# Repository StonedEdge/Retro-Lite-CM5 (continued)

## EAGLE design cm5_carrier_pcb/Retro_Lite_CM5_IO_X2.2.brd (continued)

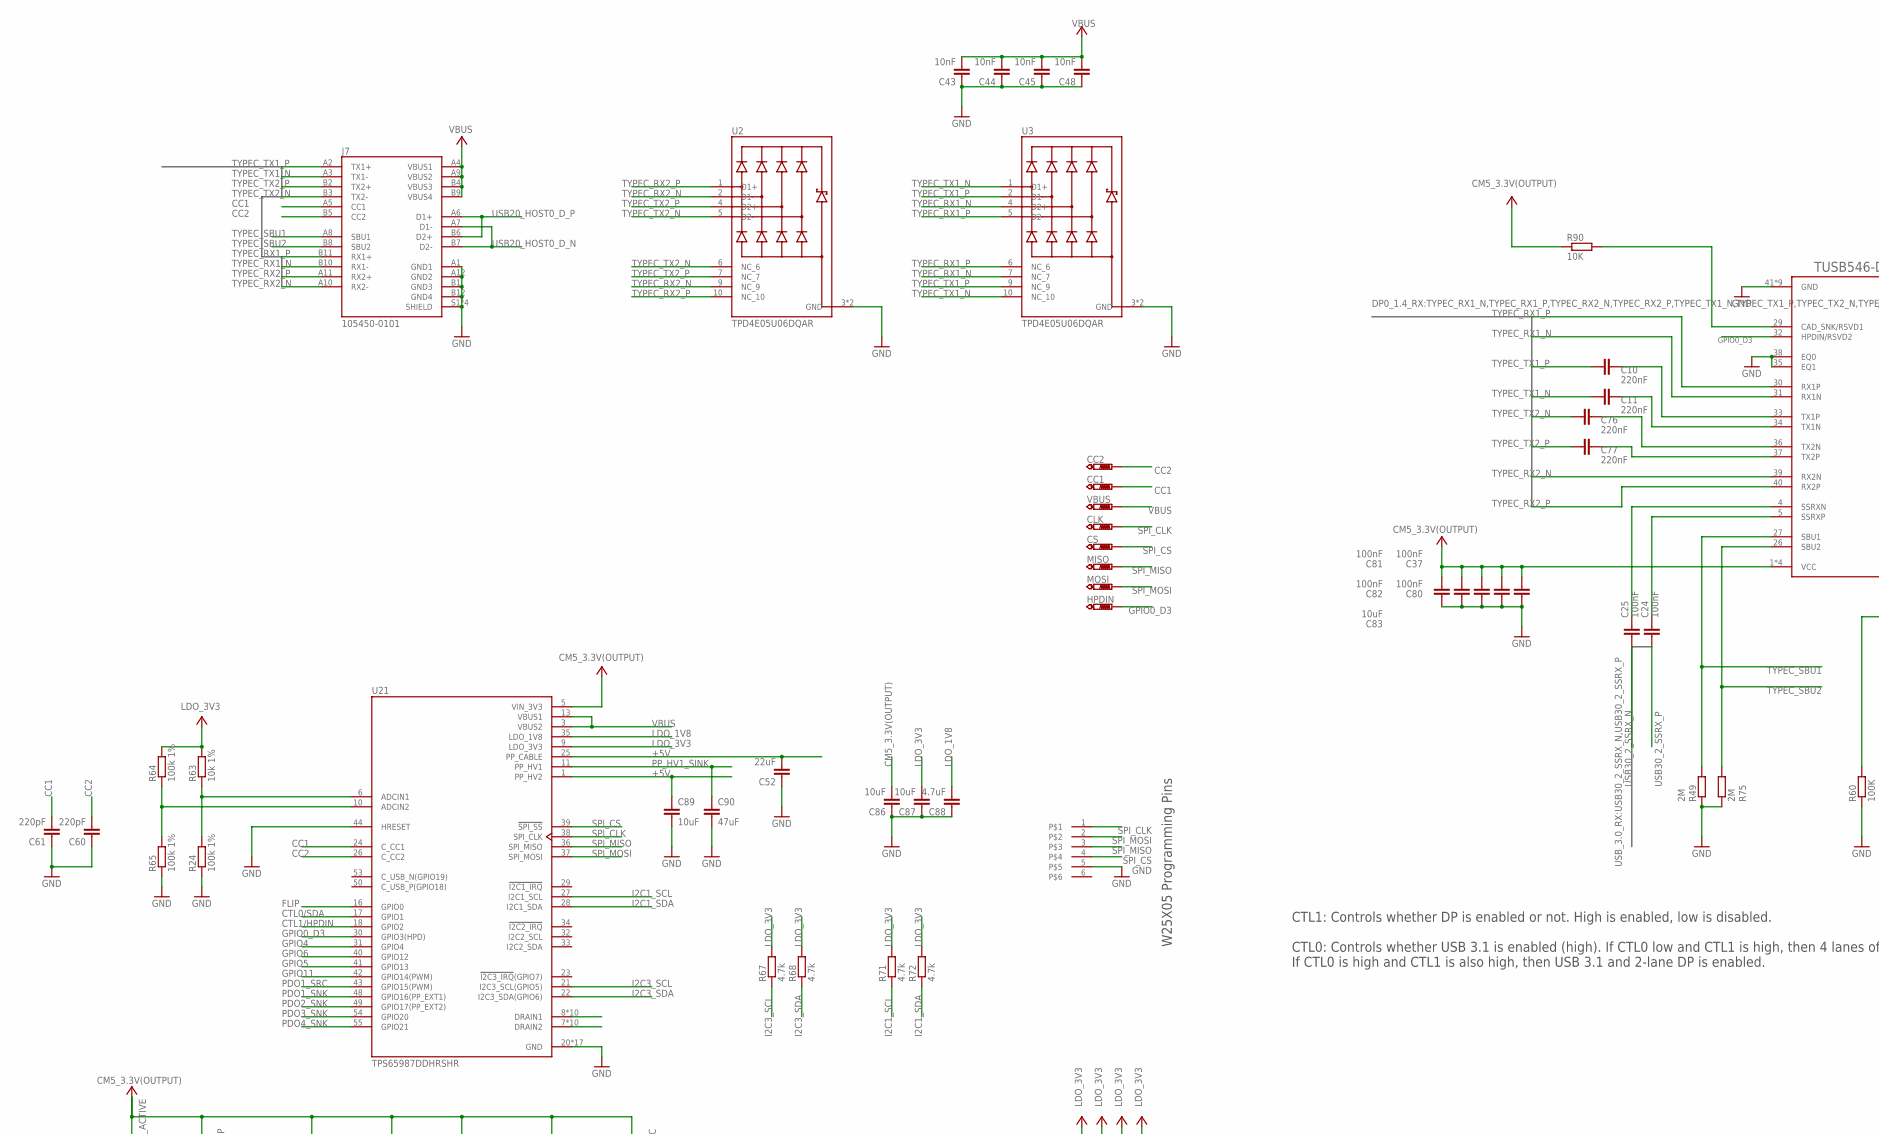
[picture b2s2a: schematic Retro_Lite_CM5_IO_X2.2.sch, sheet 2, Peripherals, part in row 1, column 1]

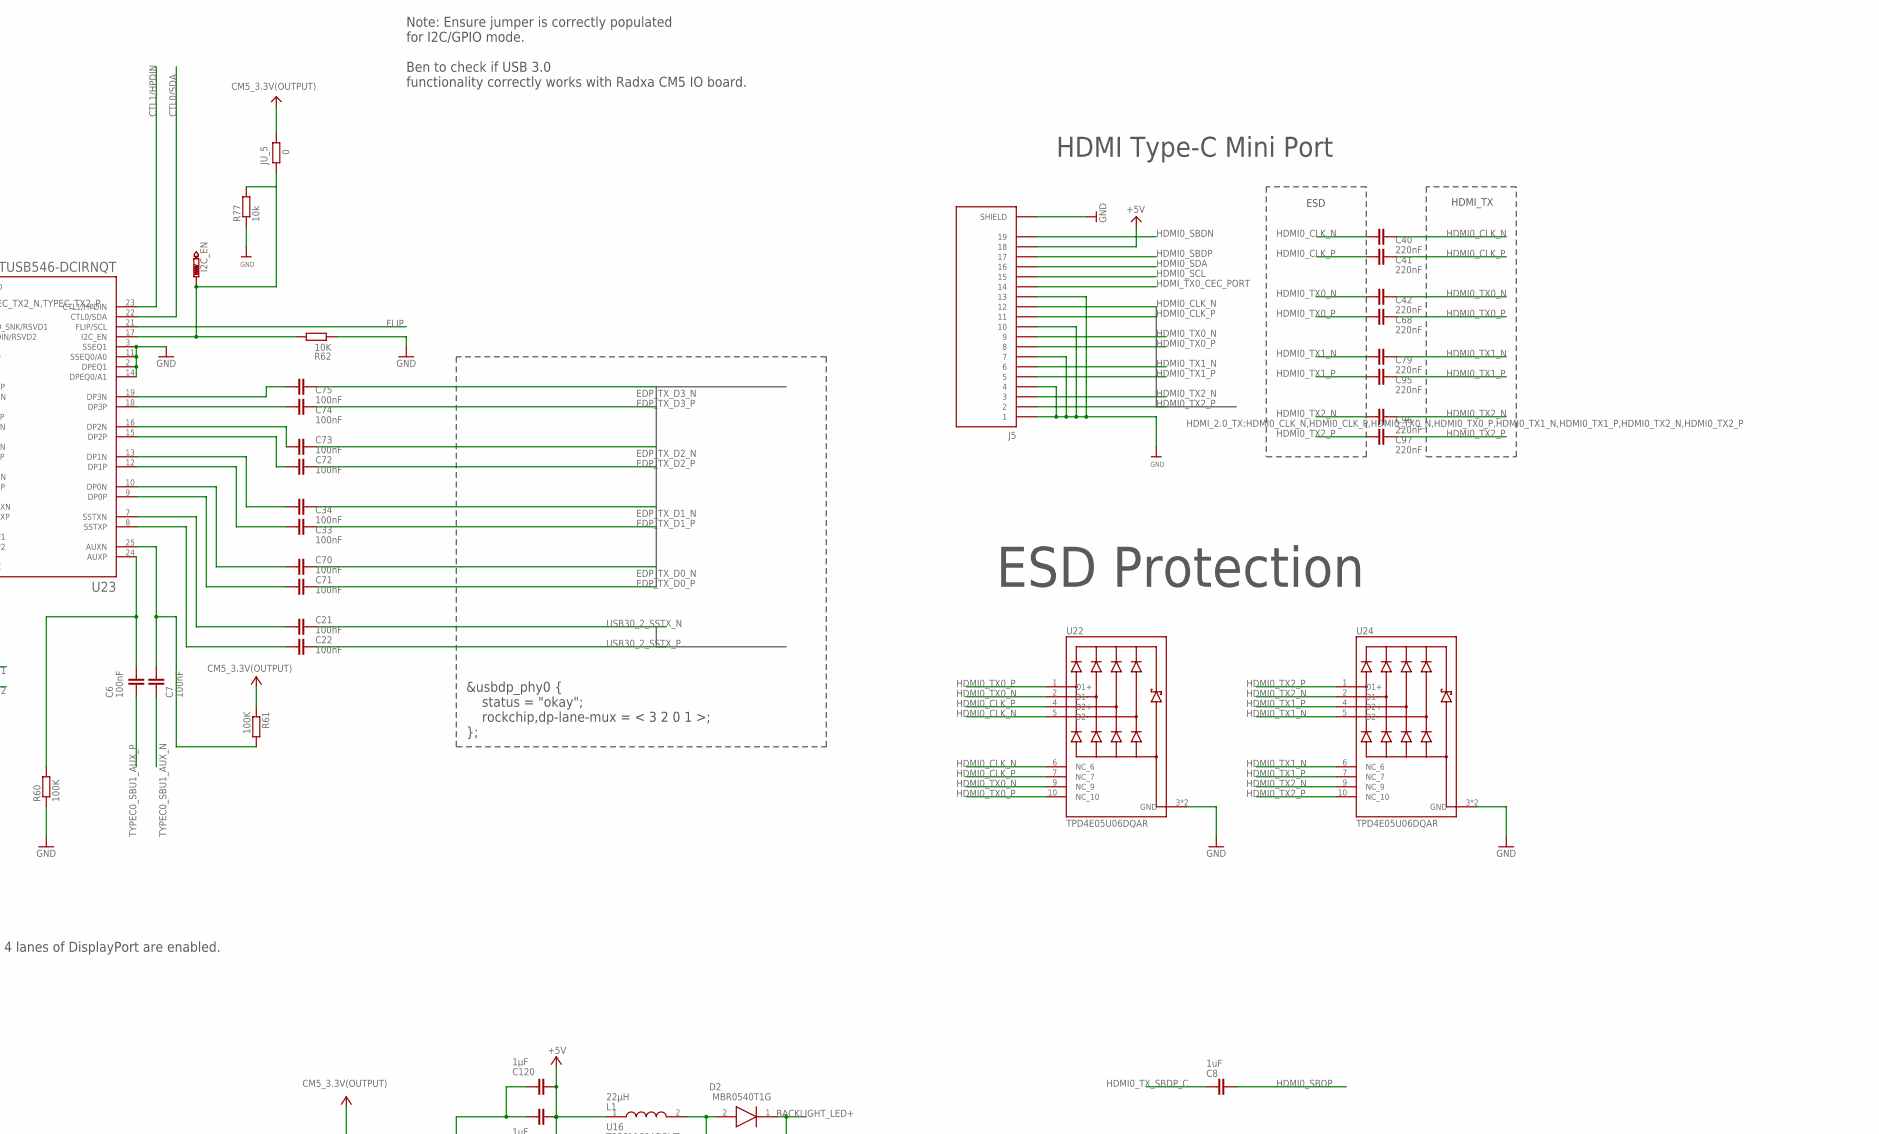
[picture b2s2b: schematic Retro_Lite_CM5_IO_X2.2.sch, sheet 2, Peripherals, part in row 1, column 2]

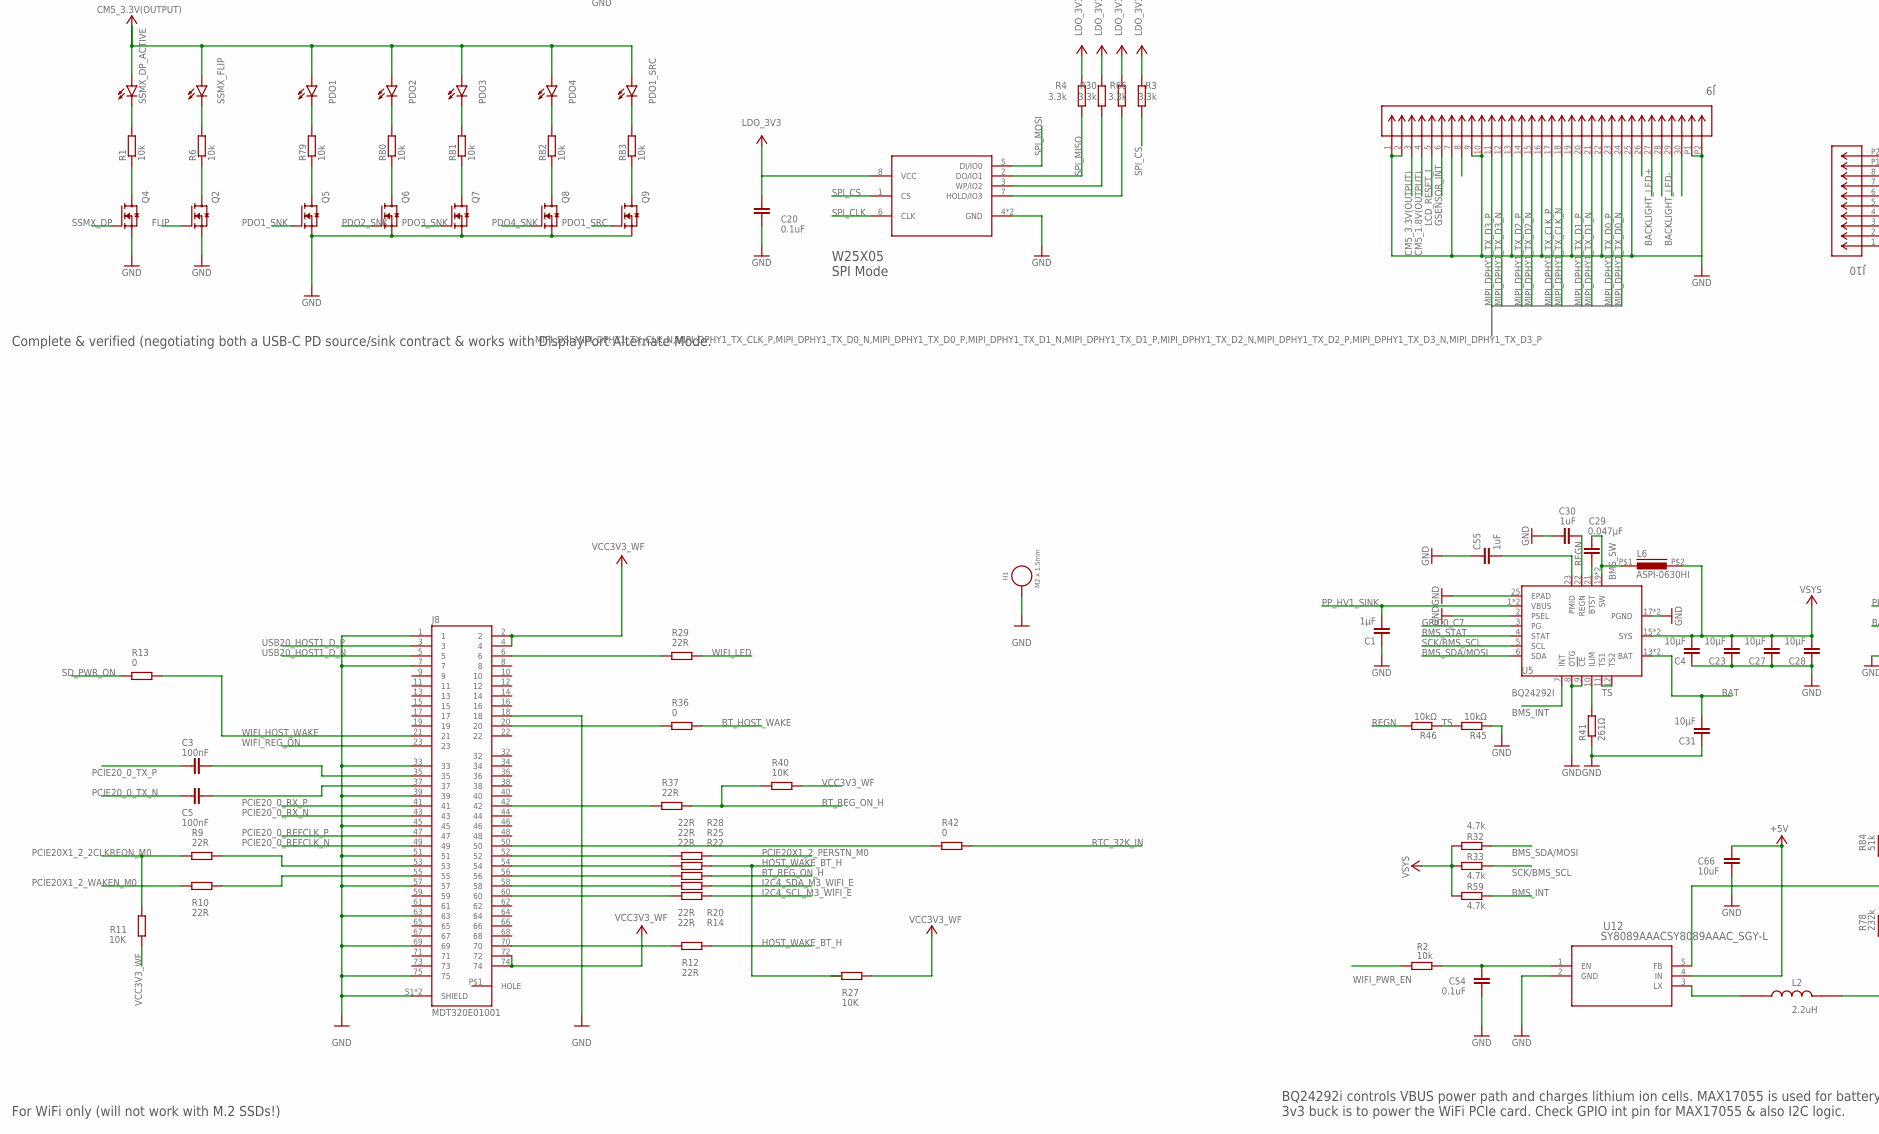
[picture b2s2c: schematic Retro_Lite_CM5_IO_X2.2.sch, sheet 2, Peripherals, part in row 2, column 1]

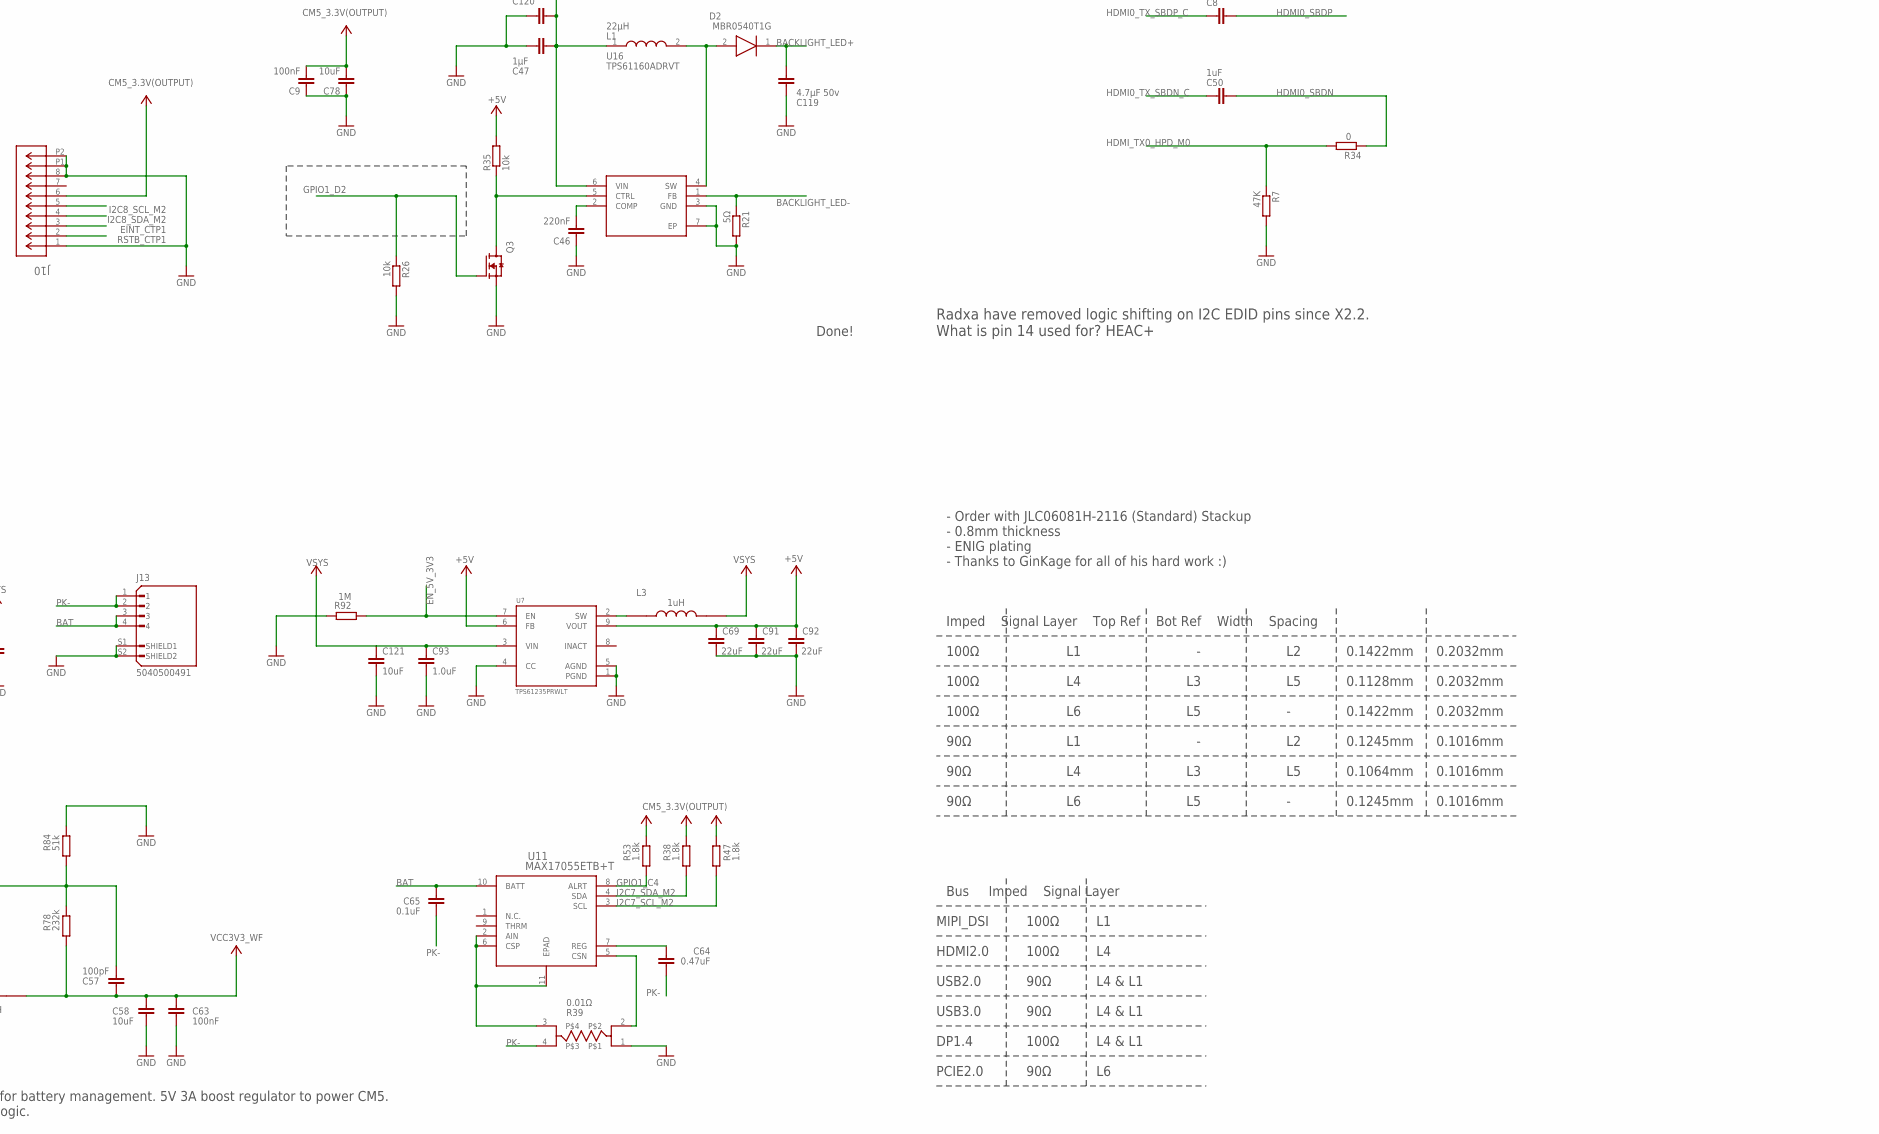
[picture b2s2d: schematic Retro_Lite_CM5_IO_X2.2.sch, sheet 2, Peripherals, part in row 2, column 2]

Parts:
C1: 1µF; C0805
C3, C5, C6, C7, C9, C21, C22, C24, C25, C33, C34, C37, C63, C70, C71, C72, C73, C74, C75, C80, C81, C82: 100nF; C0402
C4, C23, C27, C28, C31: 10µF; C0805
C8, C50: 1uF; C0402
C10, C11, C40, C41, C42, C68, C76, C77, C79, C95, C96, C97: 220nF; C0402
C20, C54, C65: 0.1uF; C0402
C29: 0.047µF; C0603
C30, C55: 1uF; C0603
C43, C44, C45, C48: 10nF; C0805
C46: 220nF; C0603
C47, C120: 1µF; C0603
C52: 22uF; C0402
C57: 100pF; C0402
C58, C66, C86, C87, C89: 10uF; C0402
C60, C61: 220pF; C0402
C64: 0.47uF; C0402
C69, C91, C92: 22uF; 0805
C78: 10uF; C0603
C83: 10uF; C0805
C88: 4.7uF; C0402
C90: 47uF; C0603
C93: 1.0uF; 0603
C119: 4.7µF 50v; C0805
C121: 10uF; 0603
CC1, CC2: PTR1TP07R; TP07R
CLK: PTR1TP07R; TP07R
CS: PTR1TP07R; TP07R
D2: MBR0540T1G; SOD3716X135N
H1: M2 x 1.5mm; WA-SMSI_9774015243
HPDIN: PTR1TP07R; TP07R
I2C_EN: PTR1TP07R; TP07R
J5: 685119136923; WURTH_685119136923
J7: 105450-0101; MOLEX_105450-0101
J8: MDT320E01001; AMPHENOL_MDT320E01001
J9: 5051103091; CON_5051103091_MOL
J10: 5051100892; CON_5051100892_MOL
J13: 5040500491; MOLEX_5040500491
JU_5: 0; R0402
L1: 22µH; VLCF4020_1
L2: 2.2uH; IND_AMDLA4530S-2R2MT
L3: 1uH; IND_SPM5020T-1R0M
L6: ASPI-0630HI
MISO: PTR1TP07R; TP07R
MOSI: PTR1TP07R; TP07R
PDO1, PDO1_SRC, PDO2, PDO3, PDO4: LEDSML0603; SML0603
Q2, Q3, Q4, Q5, Q6, Q7, Q8, Q9: AO3400A; SOT95P280X125-3N
R1, R2, R6, R77, R79, R80, R81, R82, R83: 10k; R0402
R3, R4, R30, R66: 3.3k; R0402
R7: 47K; R0402
R9, R10, R12, R14, R20, R22, R25, R28, R29, R37: 22R; R0402
R11, R27, R40, R62, R90: 10K; R0402
R13, R34, R36, R42: 0; R0402
R21: 5Ω; R0603
R24, R64, R65: 100k 1%; R0402
R26, R35: 10k; R0603
R32, R33, R59, R67, R68, R71, R72: 4.7k; R0402
R38, R47, R53: 1.8k; R0402
R39: PS0306DRF7T0R01L
R41: 261Ω; R0402
R45: 10kΩ; R0402
R46: 10kΩ; R0603
R49, R75: 2M; R0402
R60, R61: 100K; R0402
R63: 10k 1%; R0402
R78: 232k; R0402
R84: 51k; R0402
R92: 1M; R0402
SSMX_DP_ACTIVE: LEDSML0603; SML0603
SSMX_FLIP_ACTIVE: SSMX_FLIP; SML0603
U2, U3, U22, U24: TPD4E05U06DQAR; IC_TPD4E05U06DQAR
U4: W25X05CLUXIGTR; PSON50P300X200X60-9N
U5: BQ24292I; QFN50P400X400X100-25N
U7: TPS61235PRWLT; CONV_TPS61235PRWLT
U11: MAX17055ETB+T; 21-100013A_T102A2+1C_MXM
U12: SY8089AAACSY8089AAAC_SGY-L; SY8089AAAC_SGY-L
U16: TPS61160ADRVT; SON65P200X200X80-7N
U21: TPS65987DDHRSHR; IC_TPS65987DDHRSHR
U23: TUSB546-DCIRNQT; QFN40P400X600X80-41N
U$7: M.2HOLE
U$11: 6PINEADER; 1MM_PIC-PROGRAMING_HEADER
VBUS: PTR1TP07R; TP07R

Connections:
+5V: C47.1, C52.2, C66.1, C69.1, C89.1, C91.1, C92.1, C120.1, J5.18, L1.1, R35.2, U7.6 (FB), U7.9 (VOUT), U12.4 (IN), U16.6 (VIN), U21.1 (PP_HV2), U21.25 (PP_CABLE); also elsewhere on the board
BACKLIGHT_LED+: C119.1, D2.1 (K), J9.27
BACKLIGHT_LED-: J9.29, R21.1, U16.1 (FB)
BAT: C31.2, C65.1, J13.3, J13.4, U5.13 (BAT), U5.14 (BAT), U11.10 (BATT); also elsewhere on the board
BMS_INT: R59.2, U5.7 (INT); also elsewhere on the board
BMS_SDA/MOSI: R32.2, U5.6 (SDA); also elsewhere on the board
BMS_STAT: U5.4 (STAT); also elsewhere on the board
BMS_SW: C29.1, L6.P$1 (1), U5.19 (SW), U5.20 (SW)
BT_HOST_WAKE: R36.2; also elsewhere on the board
BT_REG_ON_H: R22.2, R37.2, R40.1; also elsewhere on the board
CC1: C61.2, CC1.TP, J7.A5 (CC1), U21.24 (C_CC1)
CC2: C60.2, CC2.TP, J7.B5 (CC2), U21.26 (C_CC2)
CM5_1.8V(OUTPUT): J9.4; also elsewhere on the board
CM5_3.3V(OUTPUT): C9.2, C37.2, C78.2, C80.2, C81.2, C82.2, C83.2, C86.2, J9.3, J10.6, JU_5.2, PDO1.A, PDO1_SRC.A, PDO2.A, PDO3.A, PDO4.A, R38.1, R47.1, R53.1, R61.1, R90.1, SSMX_DP_ACTIVE.A, SSMX_FLIP_ACTIVE.A, U21.5 (VIN_3V3), U23.1 (VCC), U23.6 (VCC), U23.20 (VCC), U23.28 (VCC); also elsewhere on the board
CTL0/SDA: U21.17 (GPIO1), U23.22 (CTL0/SDA)
CTL1/HPDIN: U21.18 (GPIO2), U23.23 (CTL1/HPDIN)
EDP_TX_D0_N: C70.1, C70.2, U23.10 (DP0N); also elsewhere on the board
EDP_TX_D0_P: C71.1, C71.2, U23.9 (DP0P); also elsewhere on the board
EDP_TX_D1_N: C34.1, C34.2, U23.13 (DP1N); also elsewhere on the board
EDP_TX_D1_P: C33.1, C33.2, U23.12 (DP1P); also elsewhere on the board
EDP_TX_D2_N: C73.1, C73.2, U23.16 (DP2N); also elsewhere on the board
EDP_TX_D2_P: C72.1, C72.2, U23.15 (DP2P); also elsewhere on the board
EDP_TX_D3_N: C75.1, C75.2, U23.19 (DP3N); also elsewhere on the board
EDP_TX_D3_P: C74.1, C74.2, U23.18 (DP3P); also elsewhere on the board
EINT_CTP1: J10.3; also elsewhere on the board
EN_5V_3V3: R92.2, U7.7 (EN); also elsewhere on the board
FLIP: Q2.1 (G), U21.16 (GPIO0), U23.21 (FLIP/SCL)
GND: C1.1, C4.1, C9.1, C20.1, C23.1, C27.1, C28.1, C30.1, C31.1, C37.1, C43.1, C44.1, C45.1, C46.1, C47.2, C48.1, C52.1, C54.2, C55.1, C58.2, C60.1, C61.1, C63.2, C66.2, C69.2, C78.1, C80.1, C81.1, C82.1, C83.1, C86.1, C87.1, C88.1, C89.2, C90.2, C91.2, C92.2, C93.2, C119.2, C120.2, C121.2, H1.1, J5.1, J5.4, J5.7, J5.10, J5.13, J5.S1 (SHIELD), J5.S2 (SHIELD), J5.S3 (SHIELD), J5.S4 (SHIELD), J7.A1 (GND1), J7.A12 (GND2), J7.B1 (GND3), J7.B12 (GND4), J7.S1 (SHIELD), J7.S2 (SHIELD), J7.S3 (SHIELD), J7.S4 (SHIELD), J8.1, J8.7, J8.18, J8.33, J8.39, J8.45, J8.51, J8.57, J8.63, J8.69, J8.75, J8.S1 (SHIELD), J8.S2 (SHIELD), J9.1, J9.2, J9.7, J9.9, J9.10, J9.13, J9.16, J9.19, J9.22, J9.25, J9.P1, J9.P2, J10.1, J10.8, J10.P1, J10.P2, J13.S1 (SHIELD1), J13.S2 (SHIELD2), Q2.2 (S), Q3.2 (S), Q4.2 (S), Q5.2 (S), Q6.2 (S), Q7.2 (S), Q8.2 (S), Q9.2 (S), R7.2, R21.2, R24.1, R26.2, R39.1, R41.1, R45.1, R49.1, R60.1, R62.1, R65.1, R75.1, R77.1, R84.1, R92.1, U2.3 (GND), U2.8 (GND), U3.3 (GND), U3.8 (GND), U4.4 (GND), U4.9 (GND), U5.2 (PSEL), U5.8 (OTG), U5.9 (!CE), U5.17 (PGND), U5.18 (PGND), U5.25 (EPAD), U7.1 (PGND), U7.4 (CC), U7.5 (AGND), U12.2 (GND), U16.3 (GND), U16.7 (EP), U21.20 (GND), U21.44 (HRESET), U21.45 (GND), U21.46 (GND), U21.47 (GND), U21.51 (GND), U21.59 (GND), U21.59_1 (GND), U21.59_2 (GND), U21.59_3 (GND), U21.59_4 (GND), U21.59_5 (GND), U21.59_6 (GND), U21.59_7 (GND), U21.59_8 (GND), U21.59_9 (GND), U21.59_10 (GND), U21.59_11 (GND), U22.3 (GND), U22.8 (GND), U23.2 (DPEQ1), U23.3 (SSEQ1), U23.11 (SSEQ0/A0), U23.14 (DPEQ0/A1), U23.35 (EQ1), U23.38 (EQ0), U23.41 (GND), U23.42 (GND), U23.43 (GND), U23.44 (GND), U23.45 (GND), U23.46 (GND), U23.47 (GND), U23.48 (GND), U23.49 (GND), U24.3 (GND), U24.8 (GND), U$11.5; also elsewhere on the board
GPIO0_C7: U5.3 (PG); also elsewhere on the board
GPIO0_D3: HPDIN.TP, U21.30 (GPIO3(HPD)), U23.32 (HPDIN/RSVD2); also elsewhere on the board
GPIO1_C4: R53.2, U11.8 (ALRT); also elsewhere on the board
GPIO1_D2: Q3.1 (G), R26.1; also elsewhere on the board
GPIO4: U21.31 (GPIO4)
GPIO5: U21.41 (GPIO13)
GPIO6: U21.40 (GPIO12)
GPIO11: U21.42 (GPIO14(PWM))
GSENSOR_INT: J9.6; also elsewhere on the board
HDMI0_CLK_N: C40.1, C40.2, J5.12, U22.5 (D2-), U22.6 (NC_6); also elsewhere on the board
HDMI0_CLK_P: C41.1, C41.2, J5.11, U22.4 (D2+), U22.7 (NC_7); also elsewhere on the board
HDMI0_SBDN: C50.2, J5.19, R34.1
HDMI0_SBDP: C8.2, J5.17
HDMI0_SCL: J5.15; also elsewhere on the board
HDMI0_SDA: J5.16; also elsewhere on the board
HDMI0_TX0_N: C42.1, C42.2, J5.9, U22.2 (D1-), U22.9 (NC_9); also elsewhere on the board
HDMI0_TX0_P: C68.1, C68.2, J5.8, U22.1 (D1+), U22.10 (NC_10); also elsewhere on the board
HDMI0_TX1_N: C79.1, C79.2, J5.6, U24.5 (D2-), U24.6 (NC_6); also elsewhere on the board
HDMI0_TX1_P: C95.1, C95.2, J5.5, U24.4 (D2+), U24.7 (NC_7); also elsewhere on the board
HDMI0_TX2_N: C96.1, C96.2, J5.3, U24.2 (D1-), U24.9 (NC_9); also elsewhere on the board
HDMI0_TX2_P: C97.1, C97.2, J5.2, U24.1 (D1+), U24.10 (NC_10); also elsewhere on the board
HDMI0_TX_SBDN_C: C50.1; also elsewhere on the board
HDMI0_TX_SBDP_C: C8.1; also elsewhere on the board
HDMI_TX0_CEC_PORT: J5.14; also elsewhere on the board
HDMI_TX0_HPD_M0: R7.1, R34.2; also elsewhere on the board
HOST_WAKE_BT_H: R12.2, R25.2, R27.1; also elsewhere on the board
I2C1_SCL: R71.1, U21.27 (I2C1_SCL)
I2C1_SDA: R72.1, U21.28 (I2C1_SDA)
I2C3_SCL: R67.1, U21.21 (I2C3_SCL(GPIO5))
I2C3_SDA: R68.1, U21.22 (I2C3_SDA(GPIO6))
I2C4_SCL_M3_WIFI_E: R14.2; also elsewhere on the board
I2C4_SDA_M3_WIFI_E: R20.2; also elsewhere on the board
I2C7_SCL_M2: R47.2, U11.3 (SCL); also elsewhere on the board
I2C7_SDA_M2: R38.2, U11.4 (SDA); also elsewhere on the board
I2C8_SCL_M2: J10.5; also elsewhere on the board
I2C8_SDA_M2: J10.4; also elsewhere on the board
LCD_RESET_L: J9.5; also elsewhere on the board
LDO_1V8: C88.2, U21.35 (LDO_1V8)
LDO_3V3: C20.2, C87.2, R3.2, R4.2, R30.2, R63.2, R64.2, R66.2, R67.2, R68.2, R71.2, R72.2, U4.8 (VCC), U21.9 (LDO_3V3)
MIPI_DPHY1_TX_CLK_N: J9.18; also elsewhere on the board
MIPI_DPHY1_TX_CLK_P: J9.17; also elsewhere on the board
MIPI_DPHY1_TX_D0_N: J9.24; also elsewhere on the board
MIPI_DPHY1_TX_D0_P: J9.23; also elsewhere on the board
MIPI_DPHY1_TX_D1_N: J9.21; also elsewhere on the board
MIPI_DPHY1_TX_D1_P: J9.20; also elsewhere on the board
MIPI_DPHY1_TX_D2_N: J9.15; also elsewhere on the board
MIPI_DPHY1_TX_D2_P: J9.14; also elsewhere on the board
MIPI_DPHY1_TX_D3_N: J9.12; also elsewhere on the board
MIPI_DPHY1_TX_D3_P: J9.11; also elsewhere on the board
unnamed: J8.20, R36.1
unnamed: PDO1.C, R79.2
unnamed: C57.2, R78.1, R84.2, U12.5 (FB)
unnamed: R30.1, U4.3 (WP/IO2)
unnamed: R66.1, U4.7 (HOLD/IO3)
unnamed: PDO2.C, R80.2
unnamed: R1.2, SSMX_DP_ACTIVE.C
unnamed: R6.2, SSMX_FLIP_ACTIVE.C
unnamed: Q4.3 (D), R1.1
unnamed: Q2.3 (D), R6.1
unnamed: PDO3.C, R81.2
unnamed: C5.1, J8.37
unnamed: C3.1, J8.35
unnamed: C46.2, U16.2 (COMP)
unnamed: L3.1, U7.2 (SW)
unnamed: PDO4.C, R82.2
unnamed: J8.53, R9.2
unnamed: J8.55, R10.2
unnamed: D2.2 (A), L1.2, U16.4 (SW)
unnamed: Q3.3 (D), R35.1, U16.5 (CTRL)
unnamed: J8.70, R12.1
unnamed: J8.6, R29.1
unnamed: J8.52, R28.1
unnamed: J8.54, R25.1
unnamed: J8.56, R22.1
unnamed: C55.2, U5.23 (PMID)
unnamed: C64.1, U11.7 (REG)
unnamed: C54.1, R2.1, U12.1 (EN)
unnamed: R39.2, U11.5 (CSN)
unnamed: C29.2, U5.21 (BTST)
unnamed: R41.2, U5.10 (ILIM)
unnamed: J8.58, R20.1
unnamed: R24.2, R63.1, U21.6 (ADCIN1)
unnamed: J8.60, R14.1
unnamed: J8.42, R37.1
unnamed: R39.3, U11.2 (AIN), U11.6 (CSP), U11.11 (EPAD)
unnamed: U21.8 (DRAIN1), U21.15 (DRAIN1), U21.19 (DRAIN1), U21.58 (DRAIN1), U21.58_1 (DRAIN1), U21.58_2 (DRAIN1), U21.58_3 (DRAIN1), U21.58_4 (DRAIN1), U21.58_5 (DRAIN1), U21.58_6 (DRAIN1)
unnamed: U21.7 (DRAIN2), U21.52 (DRAIN2), U21.56 (DRAIN2), U21.57 (DRAIN2), U21.57_1 (DRAIN2), U21.57_2 (DRAIN2), U21.57_3 (DRAIN2), U21.57_4 (DRAIN2), U21.57_5 (DRAIN2), U21.57_6 (DRAIN2)
unnamed: R64.1, R65.2, U21.10 (ADCIN2)
unnamed: PDO1_SRC.C, R83.2
unnamed: Q9.3 (D), R83.1
unnamed: Q8.3 (D), R82.1
unnamed: Q7.3 (D), R81.1
unnamed: C7.2, R61.2, U23.25 (AUXN)
unnamed: Q5.3 (D), R79.1
unnamed: I2C_EN.TP, JU_5.1, R62.2, R77.2, U23.17 (I2C_EN)
unnamed: Q6.3 (D), R80.1
unnamed: L2.1, U12.3 (LX)
unnamed: R90.2, U23.29 (CAD_SNK/RSVD1)
unnamed: J8.50, R42.1
PCIE20X1_2_2CLKREQN_M0: R9.1, R11.2; also elsewhere on the board
PCIE20X1_2_PERSTN_M0: R28.2; also elsewhere on the board
PCIE20X1_2_WAKEN_M0: R10.1; also elsewhere on the board
PCIE20_0_REFCLK_N: J8.49; also elsewhere on the board
PCIE20_0_REFCLK_P: J8.47; also elsewhere on the board
PCIE20_0_RX_N: J8.43; also elsewhere on the board
PCIE20_0_RX_P: J8.41; also elsewhere on the board
PCIE20_0_TX_N: C5.2; also elsewhere on the board
PCIE20_0_TX_P: C3.2; also elsewhere on the board
PDO1_SNK: Q5.1 (G), U21.48 (GPIO16(PP_EXT1))
PDO1_SRC: Q9.1 (G), U21.43 (GPIO15(PWM))
PDO2_SNK: Q6.1 (G), U21.49 (GPIO17(PP_EXT2))
PDO3_SNK: Q7.1 (G), U21.54 (GPIO20)
PDO4_SNK: Q8.1 (G), U21.55 (GPIO21)
PK-: C64.2, C65.2, J13.1, J13.2, R39.4
PP_HV1_SINK: C1.2, C90.1, U5.1 (VBUS), U5.24 (VBUS), U21.11 (PP_HV1)
REGN: C30.2, R46.2, U5.22 (REGN)
RSTB_CTP1: J10.2; also elsewhere on the board
RTC_32K_IN: R42.2; also elsewhere on the board
SCK/BMS_SCL: R33.2, U5.5 (SCL); also elsewhere on the board
SD_PWR_ON: R13.1; also elsewhere on the board
SPI_CLK: CLK.TP, U4.6 (CLK), U21.38 (SPI_CLK), U$11.1
SPI_CS: CS.TP, R3.1, U4.1 (CS), U21.39 (!SPI_SS), U$11.4
SPI_MISO: MISO.TP, R4.1, U4.2 (DO/IO1), U21.36 (SPI_MISO), U$11.3
SPI_MOSI: MOSI.TP, U4.5 (DI/IO0), U21.37 (SPI_MOSI), U$11.2
SSMX_DP: Q4.1 (G)
TS: R45.2, R46.1, U5.11 (TS1), U5.12 (TS2)
TYPEC0_SBU1_AUX_N: C7.1; also elsewhere on the board
TYPEC0_SBU1_AUX_P: C6.1, C6.2, R60.2, U23.24 (AUXP); also elsewhere on the board
TYPEC_RX1_N: J7.B10 (RX1-), U3.4 (D2+), U3.7 (NC_7), U23.31 (RX1N)
TYPEC_RX1_P: J7.B11 (RX1+), U3.5 (D2-), U3.6 (NC_6), U23.30 (RX1P)
TYPEC_RX2_N: J7.A10 (RX2-), U2.2 (D1-), U2.9 (NC_9), U23.39 (RX2N)
TYPEC_RX2_P: J7.A11 (RX2+), U2.1 (D1+), U2.10 (NC_10), U23.40 (RX2P)
TYPEC_SBU1: J7.A8 (SBU1), R49.2, U23.27 (SBU1); also elsewhere on the board
TYPEC_SBU2: J7.B8 (SBU2), R75.2, U23.26 (SBU2); also elsewhere on the board
TYPEC_TX1_N: C11.1, C11.2, J7.A3 (TX1-), U3.1 (D1+), U3.10 (NC_10), U23.34 (TX1N)
TYPEC_TX1_P: C10.1, C10.2, J7.A2 (TX1+), U3.2 (D1-), U3.9 (NC_9), U23.33 (TX1P)
TYPEC_TX2_N: C76.1, C76.2, J7.B3 (TX2-), U2.5 (D2-), U2.6 (NC_6), U23.36 (TX2N)
TYPEC_TX2_P: C77.1, C77.2, J7.B2 (TX2+), U2.4 (D2+), U2.7 (NC_7), U23.37 (TX2P)
USB20_HOST0_D_N: J7.A7 (D1-), J7.B7 (D2-); also elsewhere on the board
USB20_HOST0_D_P: J7.A6 (D1+), J7.B6 (D2+); also elsewhere on the board
USB20_HOST1_D_N: J8.5; also elsewhere on the board
USB20_HOST1_D_P: J8.3; also elsewhere on the board
USB30_2_SSRX_N: C25.1, C25.2, U23.4 (SSRXN); also elsewhere on the board
USB30_2_SSRX_P: C24.1, C24.2, U23.5 (SSRXP); also elsewhere on the board
USB30_2_SSTX_N: C21.1, C21.2, U23.7 (SSTXN); also elsewhere on the board
USB30_2_SSTX_P: C22.1, C22.2, U23.8 (SSTXP); also elsewhere on the board
VBUS: C43.2, C44.2, C45.2, C48.2, J7.A4 (VBUS1), J7.A9 (VBUS2), J7.B4 (VBUS3), J7.B9 (VBUS4), U21.3 (VBUS2), U21.13 (VBUS1), VBUS.TP
VCC3V3_WF: C57.1, C58.1, C63.1, J8.2, J8.4, J8.72, J8.74, L2.2, R11.1, R27.2, R40.2, R78.2; also elsewhere on the board
VSYS: C4.2, C23.2, C27.2, C28.2, C93.1, C121.1, L3.2, L6.P$2 (2), R32.1, R33.1, R59.1, U5.15 (SYS), U5.16 (SYS), U7.3 (VIN); also elsewhere on the board
WIFI_HOST_WAKE: J8.21, R13.2
WIFI_LED: R29.2; also elsewhere on the board
WIFI_PWR_EN: R2.2; also elsewhere on the board
WIFI_REG_ON: J8.23; also elsewhere on the board

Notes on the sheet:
100nF
R39
0.01Ω
CTL1: Controls whether DP is enabled or not. High is enabled, low is disabled. CTL0: Controls whether USB 3.1 is enabled (high). If CTL0 low and CTL1 is high, then 4 lanes of DisplayPort are enabled. If CTL0 is high and CTL1 is also high, then USB 3.1 and 2-lane DP is enabled.
Note: Ensure jumper is correctly populated for I2C/GPIO mode. Ben to check if USB 3.0 functionality correctly works with Radxa CM5 IO board.
BQ24292i controls VBUS power path and charges lithium ion cells. MAX17055 is used for battery management. 5V 3A boost regulator to power CM5. 3v3 buck is to power the WiFi PCIe card. Check GPIO int pin for MAX17055 & also I2C logic.
Complete & verified (negotiating both a USB-C PD source/sink contract & works with DisplayPort Alternate Mode.
Radxa have removed logic shifting on I2C EDID pins since X2.2. What is pin 14 used for? HEAC+
HDMI Type-C Mini Port
ESD Protection
Done!
W25X05 Programming Pins
HDMI_TX
ESD
- Order with JLC06081H-2116 (Standard) Stackup - 0.8mm thickness - ENIG plating - Thanks to GinKage for all of his hard work :)
Imped Signal Layer Top Ref Bot Ref Width Spacing
100Ω
90Ω
0.1422mm
0.1128mm
0.1245mm
0.1064mm
0.2032mm
Bus Imped Signal Layer
MIPI_DSI
HDMI2.0
USB2.0
USB3.0
DP1.4
0.1016mm
L4 & L1
PCIE2.0
W25X05 SPI Mode
For WiFi only (will not work with M.2 SSDs!)
&usbdp_phy0 { status = "okay"; rockchip,dp-lane-mux = < 3 2 0 1 >; };
